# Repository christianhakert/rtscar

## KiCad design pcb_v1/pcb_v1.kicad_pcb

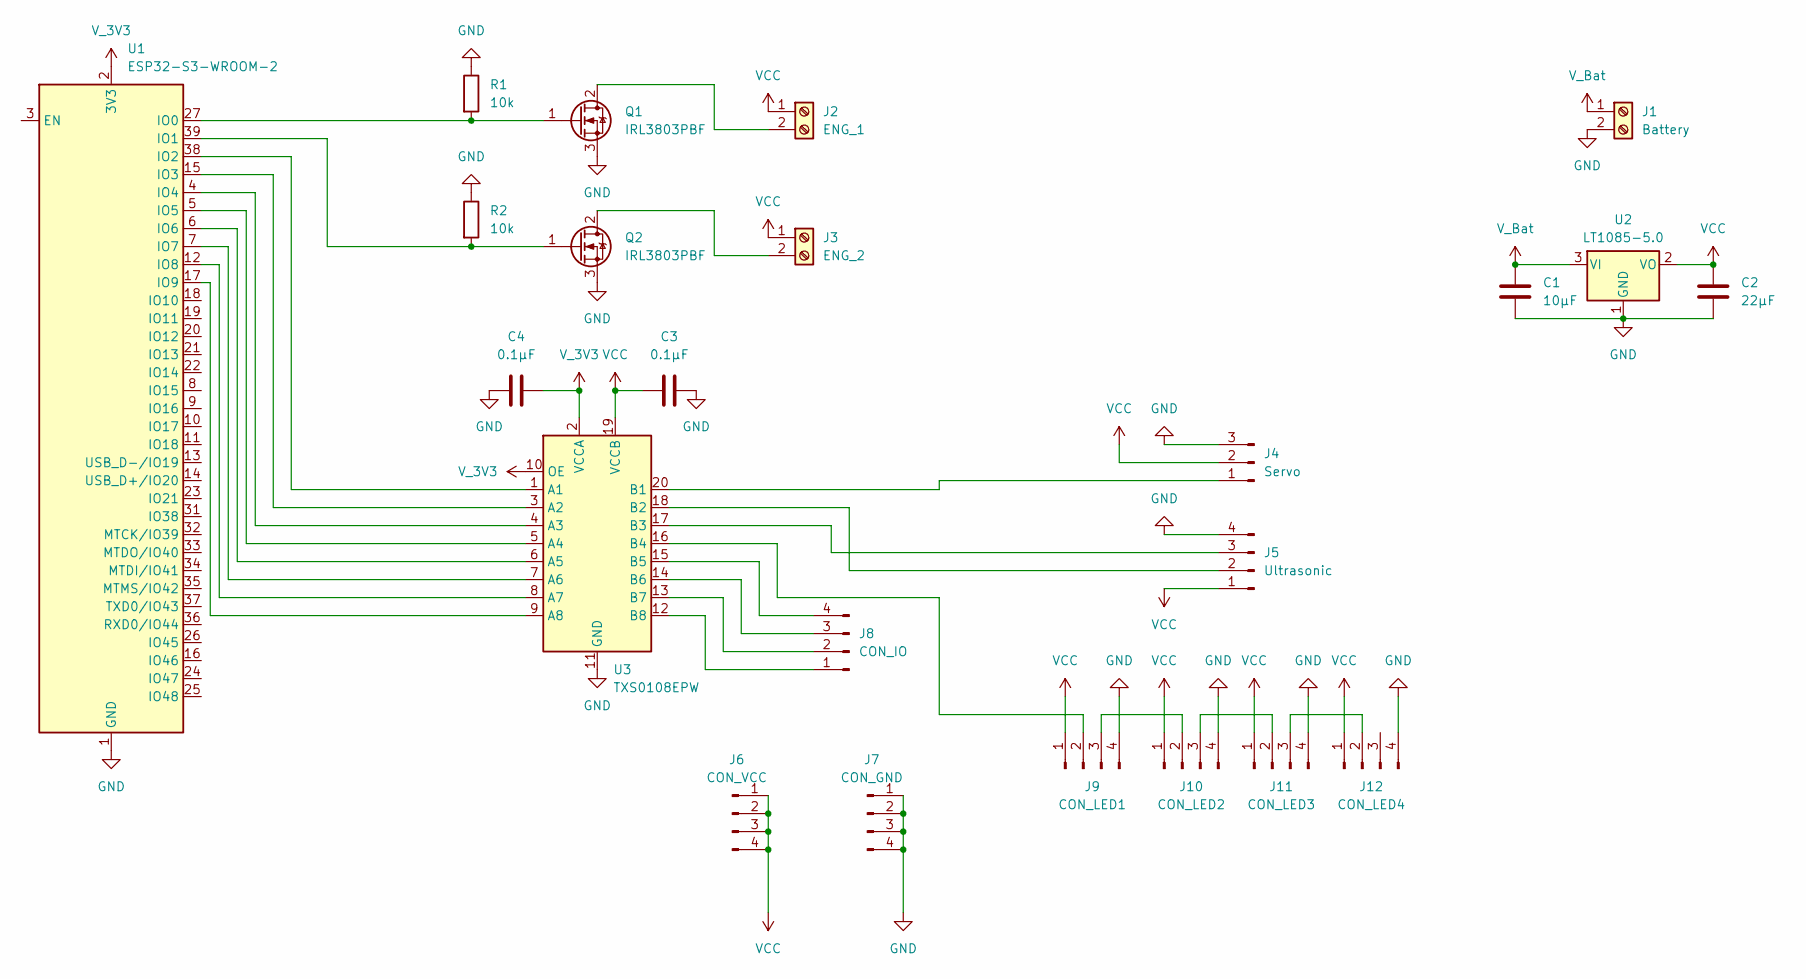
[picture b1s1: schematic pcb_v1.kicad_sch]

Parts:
C1: 10µF; C_1210_3225Metric
C2: 22µF; CP_EIA-7343-15_Kemet-W
C3, C4: 0.1µF; C_0201_0603Metric
J1: Battery; TerminalBlock_Phoenix_MKDS-1,5-2-5.08_1x02_P5.08mm_Horizont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
J2: ENG_1; TerminalBlock_Phoenix_MKDS-1,5-2-5.08_1x02_P5.08mm_Horizont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
J3: ENG_2; TerminalBlock_Phoenix_MKDS-1,5-2-5.08_1x02_P5.08mm_Horizont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
J4: Servo; Molex_KK-254_AE-6410-03A_1x03_P2.54mm_Vertical
J5: Ultrasonic; Molex_KK-254_AE-6410-04A_1x04_P2.54mm_Vertical
J6: CON_VCC; Molex_KK-254_AE-6410-04A_1x04_P2.54mm_Vertical
J7: CON_GND; Molex_KK-254_AE-6410-04A_1x04_P2.54mm_Vertical
J8: CON_IO; Molex_KK-254_AE-6410-04A_1x04_P2.54mm_Vertical
J9: CON_LED1; Molex_KK-254_AE-6410-04A_1x04_P2.54mm_Vertical
J10: CON_LED2; Molex_KK-254_AE-6410-04A_1x04_P2.54mm_Vertical
J11: CON_LED3; Molex_KK-254_AE-6410-04A_1x04_P2.54mm_Vertical
J12: CON_LED4; Molex_KK-254_AE-6410-04A_1x04_P2.54mm_Vertical
Q1, Q2: IRL3803PBF; TO-220-3_Vertical
R1, R2: 10k; R_01005_0402Metric
U1: ESP32-S3-WROOM-2
U2: LT1085-5.0; TO-220-3_Vertical
U3: TXS0108EPW; TSSOP-20_4.4x6.5mm_P0.65mm

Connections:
GND: C1.2, C2.2, C3.2, C4.1, J1.2, J4.3, J5.4, J7.1, J7.2, J7.3, J7.4, J9.4, J10.4, J11.4, J12.4, Q1.3 (S), Q2.3 (S), R1.1, R2.1, U1.1 (GND), U1.40 (GND), U1.41 (GND), U2.1 (GND), U3.11 (GND)
unnamed: J2.2, Q1.2 (D)
unnamed: J3.2, Q2.2 (D)
unnamed: J4.1, U3.20 (B1)
unnamed: J5.2, U3.18 (B2)
unnamed: J5.3, U3.17 (B3)
unnamed: J8.1, U3.12 (B8)
unnamed: J8.2, U3.13 (B7)
unnamed: J8.3, U3.14 (B6)
unnamed: J8.4, U3.15 (B5)
unnamed: J9.2, U3.16 (B4)
unnamed: J9.3, J10.2
unnamed: J10.3, J11.2
unnamed: J11.3, J12.2
unnamed: Q1.1 (G), R1.2, U1.27 (IO0)
unnamed: Q2.1 (G), R2.2, U1.39 (IO1)
unnamed: U1.38 (IO2), U3.1 (A1)
unnamed: U1.15 (IO3), U3.3 (A2)
unnamed: U1.4 (IO4), U3.4 (A3)
unnamed: U1.5 (IO5), U3.5 (A4)
unnamed: U1.6 (IO6), U3.6 (A5)
unnamed: U1.7 (IO7), U3.7 (A6)
unnamed: U1.12 (IO8), U3.8 (A7)
unnamed: U1.17 (IO9), U3.9 (A8)
VCC: C2.1, C3.1, J2.1, J3.1, J4.2, J5.1, J6.1, J6.2, J6.3, J6.4, J9.1, J10.1, J11.1, J12.1, U2.2 (VO), U3.19 (VCCB)
V_3V3: C4.2, U1.2 (3V3), U3.2 (VCCA), U3.10 (OE)
V_Bat: C1.1, J1.1, U2.3 (VI)

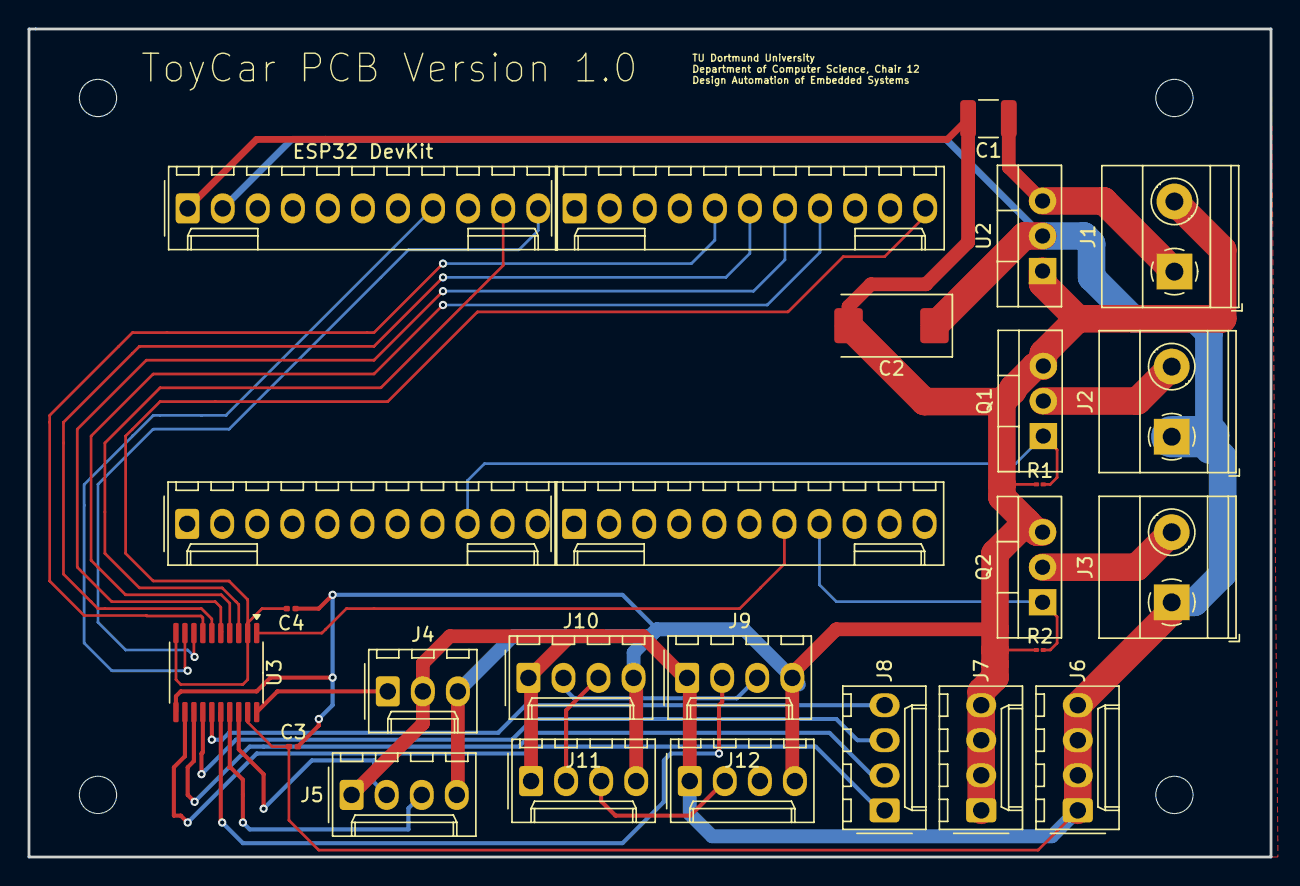
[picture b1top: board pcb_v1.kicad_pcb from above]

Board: 2 copper layers, 90.0 x 60.0 mm, 23 parts (0 on the bottom side), 19 nets.

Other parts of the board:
ESP32 DevKit: Molex_KK-254_AE-6410-11A_1x11_P2.54mm_Vertical

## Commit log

2024-10-02 add mouser list
2024-10-02 pcb design
2024-10-30 watchy firmware
2024-10-30 car firmware
2024-10-31 timer setup for servo
2024-11-04 some more imps
2024-11-05 added interface def
2024-11-05 some
2024-11-05 watchy firmware lines
2024-11-05 update watchy firmware
2024-11-05 add gyro
2024-11-06 watchy firmware done
2024-11-06 FREEDOM
2024-11-06 added freedom
2024-11-06 fixed freedom switch
2024-11-06 freedom indicator
2024-11-12 fixed drawing
2024-12-06 updated watchy firmware
2025-10-22 fix mac address
2025-10-23 uncommited changes
2025-11-06 mac address fixing
2025-11-08 MORE POWER
